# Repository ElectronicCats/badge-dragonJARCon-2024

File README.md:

# Badge DragonJARCon 2024

Badge Oficial DragonJAR 2024 el primero para una conferencia en Colombia

## Getting started

1. Connect Badge via USB to your computer.
2. Open the serial port indicated for the badge on your computer through a program such as Arduino IDE, Putty or Screen at 115200 bauds.
3. The badge text should appear in the terminal.

## Tecnologia

- ESP32C6
- LED
- Baterias 3 x AAA
- USB C
- Bateria Social

## How to build the firmware

Check the [Developer guide](./firmware/README.md) to learn how to build the firmware from scratch.

## Gratitude
Do you want to say thank you? Tag these companies on social networks and show them your badge, thanks to them it is possible

- [PCBWay](https://www.pcbway.com/)
- [TPX](https://tpx.mx/)
- [ElectronicCats](https://electroniccats.com/)

## License

Electronic Cats invests time and resources providing this open source design, please support Electronic Cats and open-source hardware by purchasing products from Electronic Cats!

Designed by Electronic Cats.

Hardware released under an CERN Open Hardware Licence v1.2. See the LICENSE_HARDWARE file for more information.

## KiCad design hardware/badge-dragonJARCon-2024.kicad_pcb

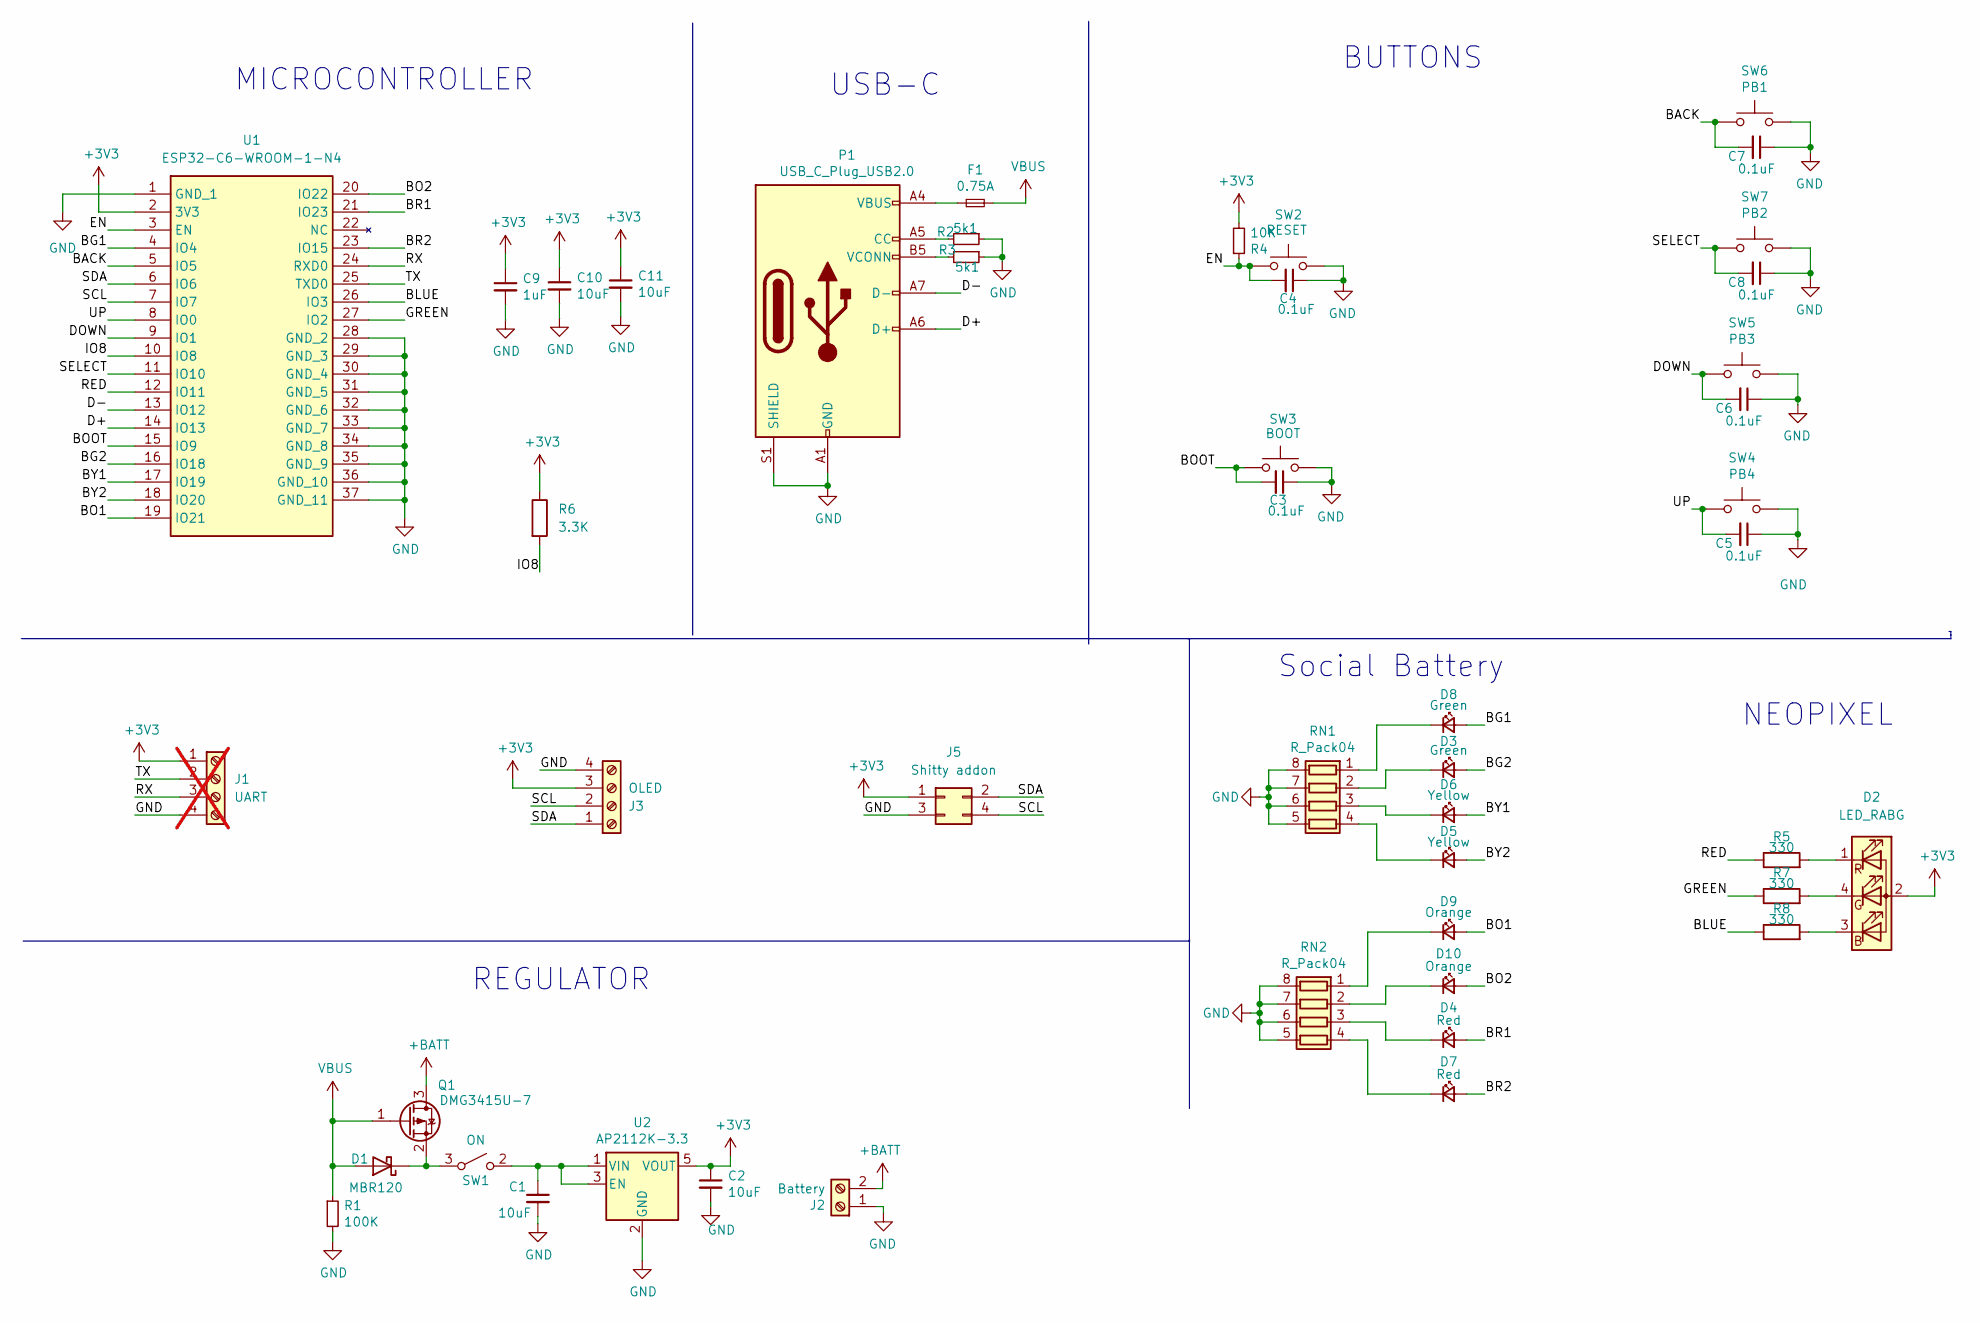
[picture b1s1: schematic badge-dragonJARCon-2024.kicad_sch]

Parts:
C1, C2, C10, C11: 10uF; C_0603_1608Metric; LCSC# C85713
C3, C4, C5, C6, C7, C8: 0.1uF; C_0603_1608Metric; LCSC# C282670
C9: 1uF; C_0603_1608Metric; LCSC# C15849
D1: MBR120; D_SOD-123F; LCSC# C130880
D2: LED_RABG; AAA3528SURKCGKC09
D3, D8: Green; LED_0805_2012Metric; LCSC# C965815
D4, D7: Red; LED_0805_2012Metric; LCSC# C965812
D5, D6: Yellow; LED_0805_2012Metric; LCSC# C84261
D9, D10: Orange; LED_0805_2012Metric; LCSC# C434437
F1: 0.75A; Fuse_0603_1608Metric; LCSC# C182438
J1: UART; PinHeader_1x04_P2.54mm_Vertical; not fitted
J2: Battery; BAT-TH_BH-AAA-A1AJ024; LCSC# C5290193
J3: OLED; Display OLED 128 x32
J5: Shitty addon; PinHeader_2x02_P2.54mm_Vertical; LCSC# C2977590
P1: USB_C_Plug_USB2.0; C393939; LCSC# C393939
Q1: DMG3415U-7; SOT-23; LCSC# C96616
R1: 100K; R_0603_1608Metric; LCSC# C25803
R2, R3: 5k1; R_0603_1608Metric; LCSC# C269696
R4: 10K; R_0603_1608Metric; LCSC# C217281
R5, R7, R8: 330; R_0603_1608Metric; LCSC# C25231
R6: 3.3K; R_0603_1608Metric; LCSC# C118393
RN1, RN2: R_Pack04; R_Array_Convex_4x0603; LCSC# C12018
SW1: ON; MSK12C02; LCSC# C431540
SW2: RESET; SW_SPST_TL3342; LCSC# C318889
SW3: BOOT; SW_SPST_TL3342; LCSC# C318889
SW4: PB4; SW_SPST_TL3342; LCSC# C318889
SW5: PB3; SW_SPST_TL3342; LCSC# C318889
SW6: PB1; SW_SPST_TL3342; LCSC# C318889
SW7: PB2; SW_SPST_TL3342; LCSC# C318889
U1: ESP32-C6-WROOM-1-N4; ESP32C6WROOM1N4; Mouser Part Number 356-ESP32C6WROOM1N4
U2: AP2112K-3.3; SOT-23-5; LCSC# C51118

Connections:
+3V3: C2.1, C9.1, C10.1, C11.1, D2.2 (A), J1.1, J3.3, J5.1, R4.2, R6.1, U1.2 (3V3), U2.5 (VOUT)
+BATT: J2.2, Q1.3 (D)
/BACK: C7.2, SW6.2, U1.5 (IO5)
/BG1: D8.2 (A), U1.4 (IO4)
/BG2: D3.2 (A), U1.16 (IO18)
/BLUE: R8.1, U1.26 (IO3)
/BO1: D9.2 (A), U1.19 (IO21)
/BO2: D10.2 (A), U1.20 (IO22)
/BOOT: C3.2, SW3.2, U1.15 (IO9)
/BR1: D4.2 (A), U1.21 (IO23)
/BR2: D7.2 (A), U1.23 (IO15)
/BY1: D6.2 (A), U1.17 (IO19)
/BY2: D5.2 (A), U1.18 (IO20)
/D+: P1.A6 (D+), U1.14 (IO13)
/D-: P1.A7 (D-), U1.13 (IO12)
/DOWN: C6.2, SW5.2, U1.9 (IO1)
/EN: C4.2, R4.1, SW2.2, U1.3 (EN)
/GREEN: R7.1, U1.27 (IO2)
/IO8: R6.2, U1.10 (IO8)
/RED: R5.1, U1.12 (IO11)
/RX: J1.3, U1.24 (RXD0)
/SCL: J3.2, J5.4, U1.7 (IO7)
/SDA: J3.1, J5.2, U1.6 (IO6)
/SELECT: C8.2, SW7.2, U1.11 (IO10)
/TX: J1.2, U1.25 (TXD0)
/UP: C5.2, SW4.2, U1.8 (IO0)
GND: C1.2, C2.2, C3.1, C4.1, C5.1, C6.1, C7.1, C8.1, C9.2, C10.2, C11.2, J1.4, J2.1, J3.4, J5.3, P1.A1 (GND), P1.A12 (GND), P1.B1 (GND), P1.B12 (GND), P1.S1 (SHIELD), R1.2, R2.1, R3.1, RN1.5 (R4.2), RN1.6 (R3.2), RN1.7 (R2.2), RN1.8 (R1.2), RN2.5 (R4.2), RN2.6 (R3.2), RN2.7 (R2.2), RN2.8 (R1.2), SW2.1, SW3.1, SW4.1, SW5.1, SW6.1, SW7.1, U1.1 (GND_1), U1.28 (GND_2), U1.29 (GND_3), U1.30 (GND_4), U1.31 (GND_5), U1.32 (GND_6), U1.33 (GND_7), U1.34 (GND_8), U1.35 (GND_9), U1.36 (GND_10), U1.37 (GND_11), U2.2 (GND)
unnamed: D1.1 (K), Q1.2 (S), SW1.3 (A)
unnamed: D2.3 (BK), R8.2
unnamed: D2.4 (GK), R7.2
unnamed: D2.1 (RK), R5.2
unnamed: D3.1 (K), RN1.2 (R2.1)
unnamed: D4.1 (K), RN2.3 (R3.1)
unnamed: D5.1 (K), RN1.4 (R4.1)
unnamed: D6.1 (K), RN1.3 (R3.1)
unnamed: D7.1 (K), RN2.4 (R4.1)
unnamed: D8.1 (K), RN1.1 (R1.1)
unnamed: D9.1 (K), RN2.1 (R1.1)
unnamed: D10.1 (K), RN2.2 (R2.1)
unnamed: F1.1, P1.A4 (VBUS), P1.A9 (VBUS), P1.B4 (VBUS), P1.B9 (VBUS)
unnamed: P1.A5 (CC), R2.2
unnamed: P1.B5 (VCONN), R3.2
unnamed: C1.1, SW1.2 (B), U2.1 (VIN), U2.3 (EN)
VBUS: D1.2 (A), F1.2, Q1.1 (G), R1.1

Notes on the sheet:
USB-C
NEOPIXEL
Social Battery
REGULATOR
BUTTONS
MICROCONTROLLER

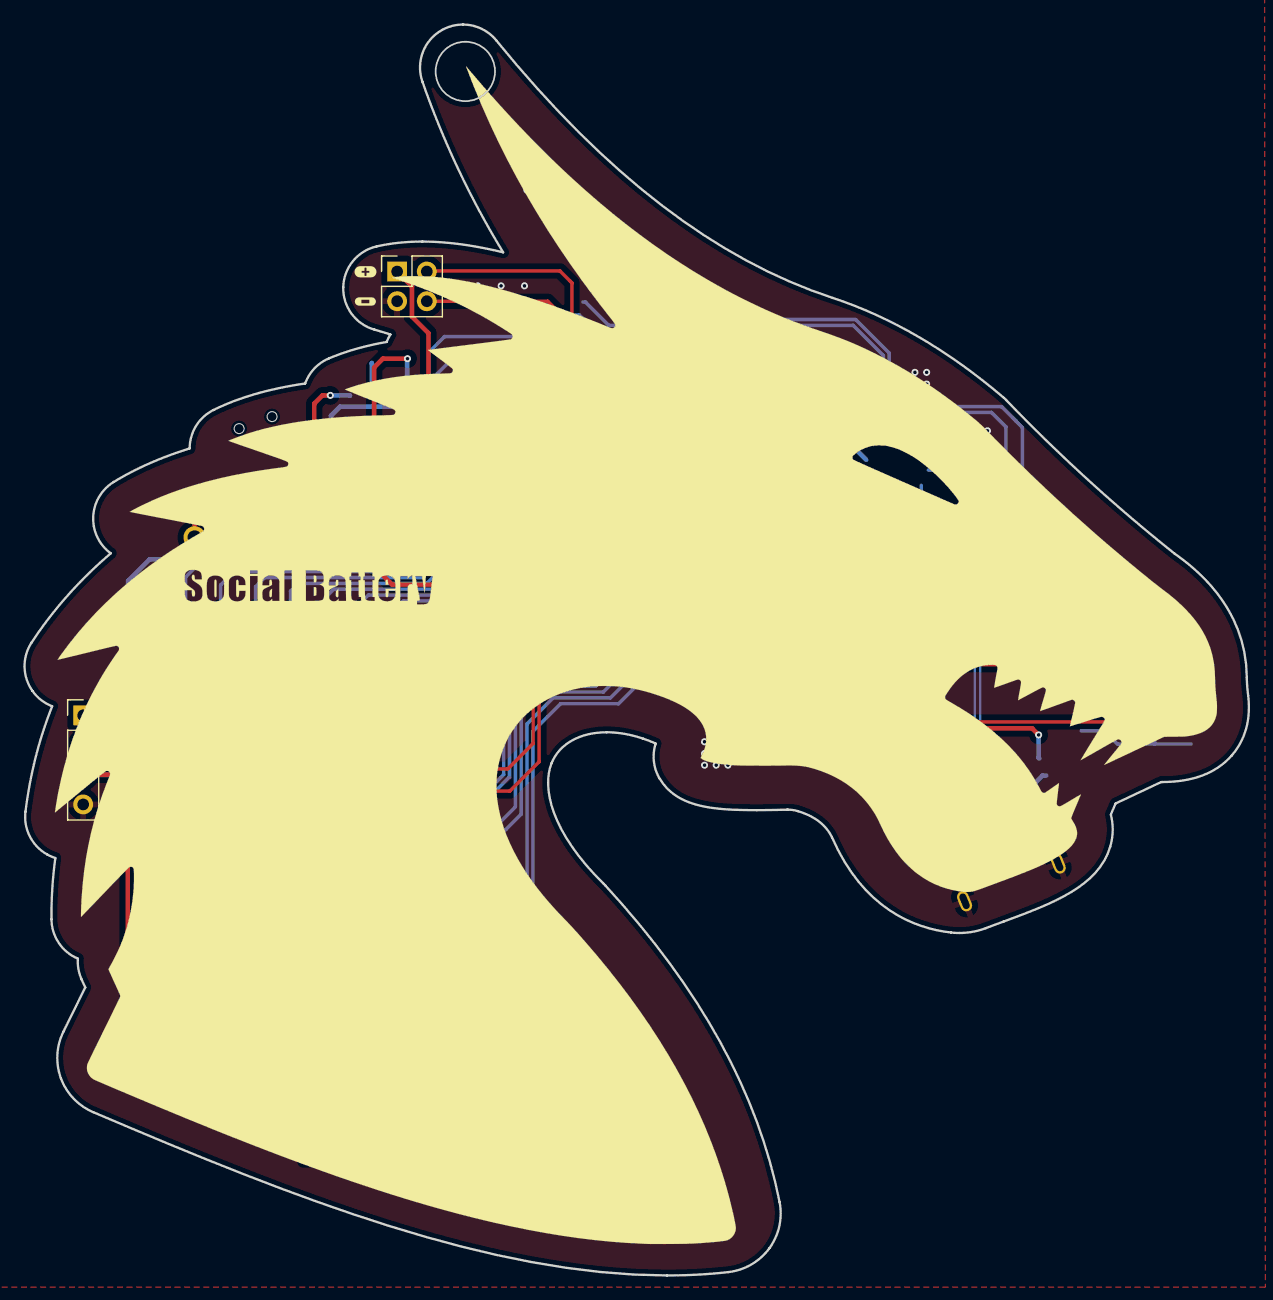
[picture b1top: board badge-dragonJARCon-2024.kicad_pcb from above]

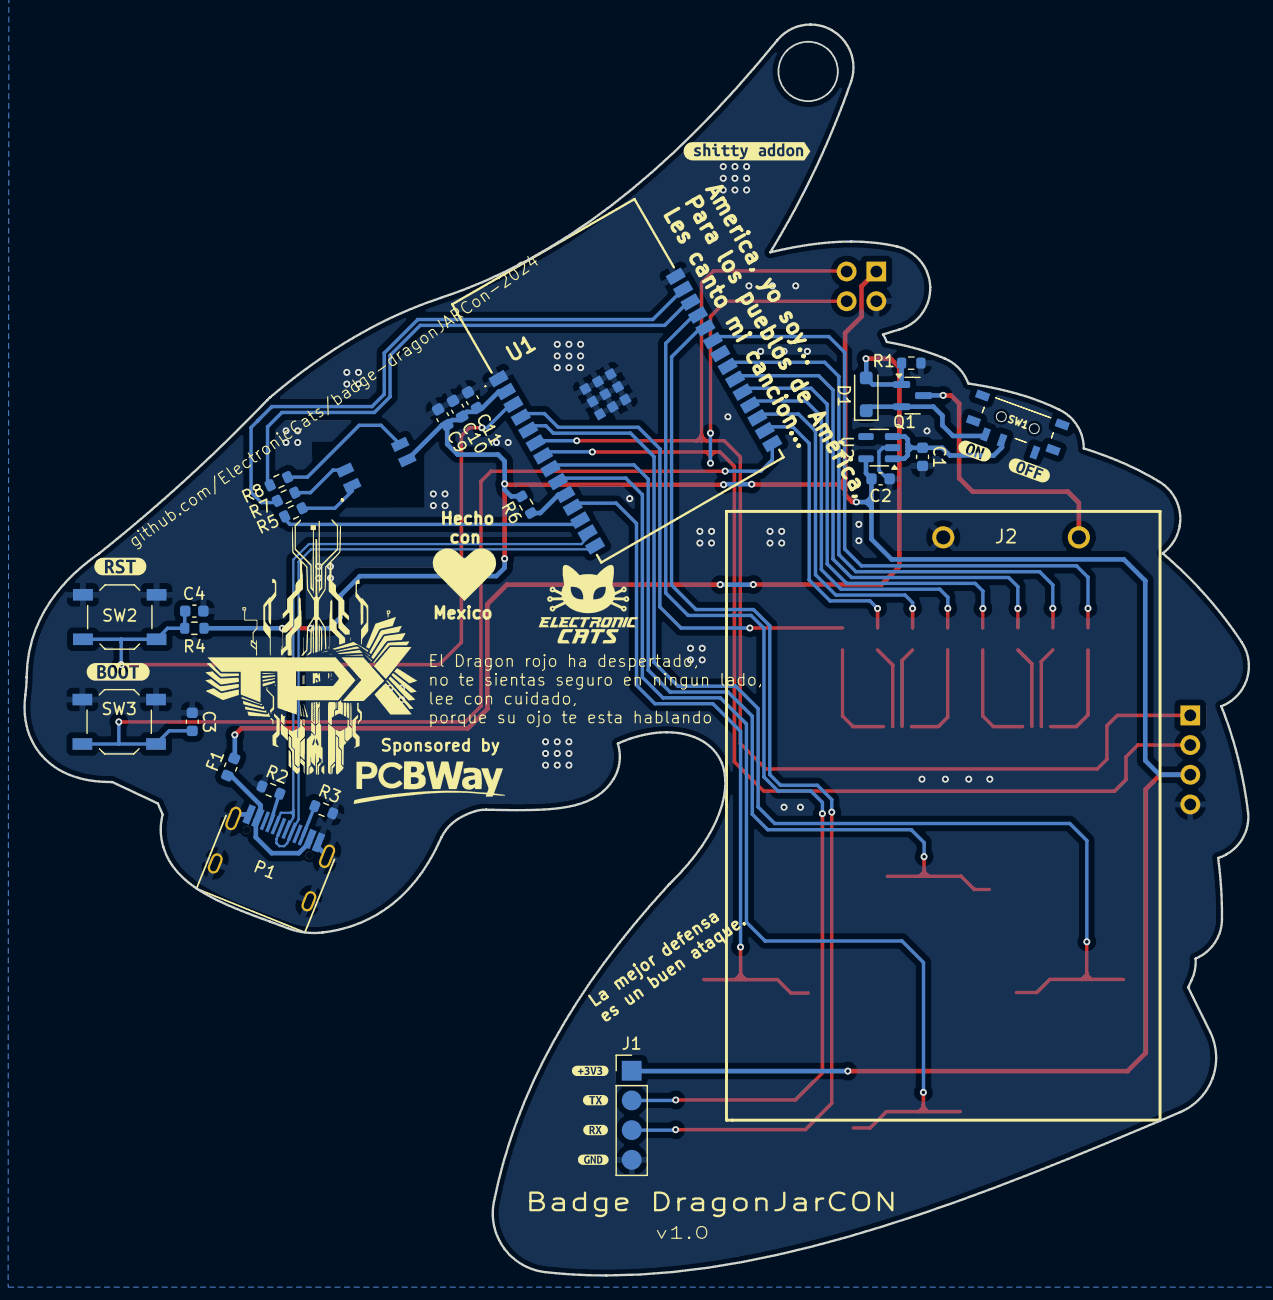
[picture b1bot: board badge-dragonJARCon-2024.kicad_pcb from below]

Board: 2 copper layers, 104.7 x 107.0 mm, 61 parts (36 on the bottom side), 44 nets.

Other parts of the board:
Ref**: Val**; Badge_DragonJAR_2024_Ojo
Ref**#2: Val**; Badge_DragonJAR_2024_cuerpo
Ref**#3: Val**; heart
kibuzzard-66425A5E: G***; kibuzzard-66425A5E
kibuzzard-66425A11: G***; kibuzzard-66425A11
kibuzzard-66450F45: G***; kibuzzard-66450F45
kibuzzard-664257DB: G***; kibuzzard-664257DB
kibuzzard-664258CC: G***; kibuzzard-664258CC
kibuzzard-664258F1: G***; kibuzzard-664258F1
kibuzzard-664510CB: G***; kibuzzard-664510CB
kibuzzard-664510D9: G***; kibuzzard-664510D9
kibuzzard-6642586D: G***; kibuzzard-6642586D
kibuzzard-6642590C: G***; kibuzzard-6642590C
kibuzzard-66425921: G***; kibuzzard-66425921

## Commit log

2024-04-30 feat(Hw): Init schematic
2024-05-02 feat(Hw): Init floorplan
2024-05-08 feat(Hw): Start new floorplan
2024-05-10 feat(Hw): Init routing
2024-05-13 feat(Hw): Update PCB
2024-05-14 feat(hw): add logos
2024-05-15 feat(hw): add links
2024-05-15 feat: Update README.md
2024-05-15 feat(): add more labels
2024-05-16 feat(Hw): Labels moved
2024-06-21 feat(Hw): Update BOM
2024-06-21 feat(Hw): Revisado
2024-08-08 fix(Hw): update labels
2024-08-13 feat(hw): add labels
2024-08-31 feat: add idf project
2024-08-31 chore: update rules
2024-08-31 chore: add config files
2024-08-31 chore: add instructions for linking the minino project
2024-09-02 docs: add link to dev guide
2024-09-02 feat: defaults for badge hardware
2024-09-02 fix: ignore main.c from minino
2024-09-02 fix: ignore menus.h from minino
2024-09-02 remove kconfig
2024-09-02 feat: add badge_connect
2024-09-03 feat: add badge link module
2024-09-03 fix: display badge finder help menu
2024-09-04 feat: get infected & show state
2024-09-06 feat: vaccines builder
2024-09-09 feat: Keyboard interaction
2024-09-09 feat: Add bitmaps
2024-09-09 chore: add keyboard default pins
2024-09-09 refactor: infection scenes
2024-09-10 fix: badge link keyboard cb
2024-09-10 chore: add badge link as submodule
2024-09-10 chore: remove .gitmodules
2024-09-10 chore: add badge_connect_bin as a submodule
2024-09-10 refactor: move project to firmware dir
2024-09-10 docs: fix broken link to developer guide
2024-09-10 docs: add how to get the submodules
2024-09-10 feat: add infection help
2024-09-10 feat: set badge as dragonjar
2024-09-10 Revert "Merge branch 'engine' into infection"
    This reverts commit 71ae5ceb1b01bfa7aed33134ec2961d1e29e356f, reversing
    changes made to 0f3dda3dca5f408185f09766dc0d7c6dd2d84f50.
2024-09-10 feat: only healty badges send vaccines
2024-09-10 feat: Delete bitmaps
2024-09-10 fix: send vaccine condition
2024-09-11 feat: add vaccination files
2024-09-11 fix: vaccination
2024-09-11 feat: vaccination is working
2024-09-11 refactor: get vaccinated
2024-09-11 feat: temporal inmunity
2024-09-11 refactor: timer
2024-09-12 refactor: infection state screens
2024-09-12 refactor: infection defense & dice roll
2024-09-13 refactor: vaccines builder
2024-09-13 refactor: 4 variants per component
2024-09-13 feat: inmunity improved
2024-09-13 feat: transmission improved
2024-09-17 feat: add baby dragon bitmap
2024-09-17 feat: healty dice roll & saved badges count & block infection menu
2024-09-18 refactor: sequence length increased
2024-09-18 refactor: reallocate help menus
2024-09-18 refactor: infected dice roll win probability decreased
2024-09-18 fix: Sequence time
2024-09-18 refactor: dice roll win probability inverted
2024-09-19 refactor: infection instructions
2024-09-19 refactor: vaccines builder improved
2024-09-19 refactor: up & down actions inverted in vaccines builder
2024-09-19 fix: vaccine receiver help
2024-09-19 feat: Add leds
2024-09-19 feat: Add sbattery
    - Arduino example
2024-09-20 feat: add a secret hint
2024-09-20 refactor: improve sequence win case
2024-09-20 refactor: increase critical state time
2024-09-20 feat: leds fork
2024-09-20 refactor: clean comments
2024-09-21 feat: Add Menu Sbattery
2024-09-23 feat: save the found badge info using preferences
2024-09-23 feat: display counter of found badges
2024-09-23 refactor: leds_d.c
2024-09-23 fix: leds on
2024-09-23 feat: remove SD card menus
2024-09-23 feat: show infection instructions when virus starts
2024-09-23 feat: remove gps apps from default sdk config
2024-09-23 feat: disable leds and buzzer by default
2024-09-23 feat: master cure
2024-09-23 refactor: remove zigbee light menu
2024-09-23 feat: Add RGB
2024-09-24 feat: Fix LEDS
2024-09-24 feat: Fix battery status
2024-09-24 feat: Fix LEDS state
2024-09-24 feat: leds notification task
2024-09-24 feat: Change notification
2024-09-26 fix: decrypt text upon vaccination
2024-09-27 feat: No infection
2024-09-27 fix: mounting sd card
2024-09-27 feat: RSSI
2024-09-27 feat: Fix File system
2024-09-27 feat: Mount
